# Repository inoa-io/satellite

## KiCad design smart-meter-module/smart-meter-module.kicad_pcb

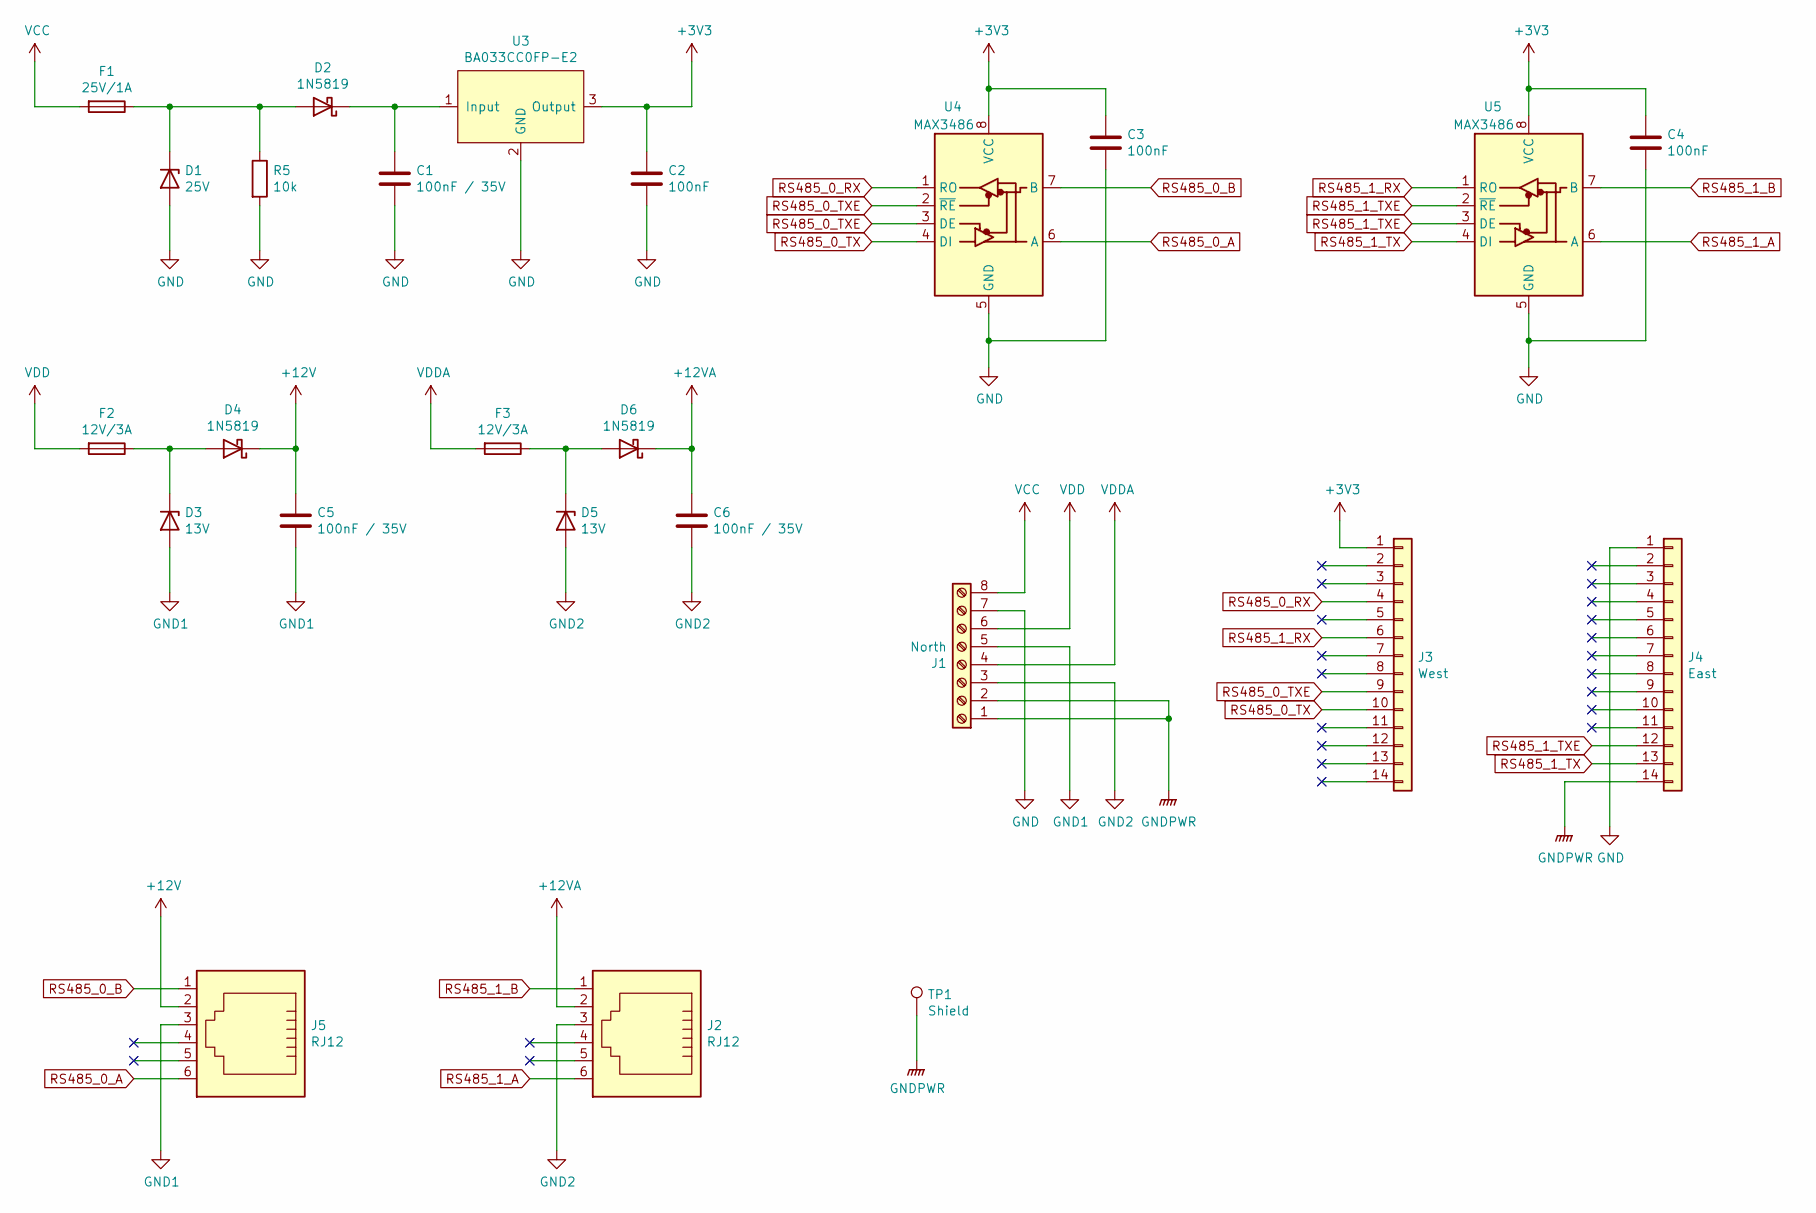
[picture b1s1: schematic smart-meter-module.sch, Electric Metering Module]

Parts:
C1, C5, C6: 100nF / 35V; C_1206_3216Metric_Pad1.33x1.80mm_HandSolder
C2, C3, C4: 100nF; C_1206_3216Metric_Pad1.33x1.80mm_HandSolder
D1: 25V; D_SOD-523
D2, D4, D6: 1N5819; D_SOD-323_HandSoldering
D3, D5: 13V; D_SOD-523
F1: 25V/1A; Fuse_1206_3216Metric_Pad1.42x1.75mm_HandSolder
F2, F3: 12V/3A; Fuse_1206_3216Metric_Pad1.42x1.75mm_HandSolder
J1: North; PHOENIX_1727078
J2, J5: RJ12; Molex-95501-6669-MFG
J3: West; PinHeader_1x14_P2.54mm_Vertical
J4: East; PinHeader_1x14_P2.54mm_Vertical
R5: 10k; R_1206_3216Metric_Pad1.30x1.75mm_HandSolder
TP1: Shield; TestPoint_Pad_D4.0mm
U3: BA033CC0FP-E2; TO-252-3_TabPin2
U4, U5: MAX3486; SOIC-8_3.9x4.9mm_P1.27mm

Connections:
+3V3: C2.1, C3.1, C4.1, J3.1, U3.3 (Output), U4.8 (VCC), U5.8 (VCC)
+12V: C5.1, D4.1 (K), J5.2
+12VA: C6.1, D6.1 (K), J2.2
GND: C1.2, C2.2, C3.2, C4.2, D1.2 (A), J1.7, J4.1, R5.2, U3.2 (GND), U4.5 (GND), U5.5 (GND)
GND1: C5.2, D3.2 (A), J1.5, J5.3
GND2: C6.2, D5.2 (A), J1.3, J2.3
GNDPWR: J1.1, J1.2, J4.14, TP1.1
unnamed: C1.1, D2.1 (K), U3.1 (Input)
unnamed: D1.1 (K), D2.2 (A), F1.1, R5.1
unnamed: D3.1 (K), D4.2 (A), F2.1
unnamed: D5.1 (K), D6.2 (A), F3.1
RS485_0_A: J5.6, U4.6 (A)
RS485_0_B: J5.1, U4.7 (B)
RS485_0_RX: J3.4, U4.1 (RO)
RS485_0_TX: J3.10, U4.4 (DI)
RS485_0_TXE: J3.9, U4.2 (~RE), U4.3 (DE)
RS485_1_A: J2.6, U5.6 (A)
RS485_1_B: J2.1, U5.7 (B)
RS485_1_RX: J3.6, U5.1 (RO)
RS485_1_TX: J4.13, U5.4 (DI)
RS485_1_TXE: J4.12, U5.2 (~RE), U5.3 (DE)
VCC: F1.2, J1.8
VDD: F2.2, J1.6
VDDA: F3.2, J1.4

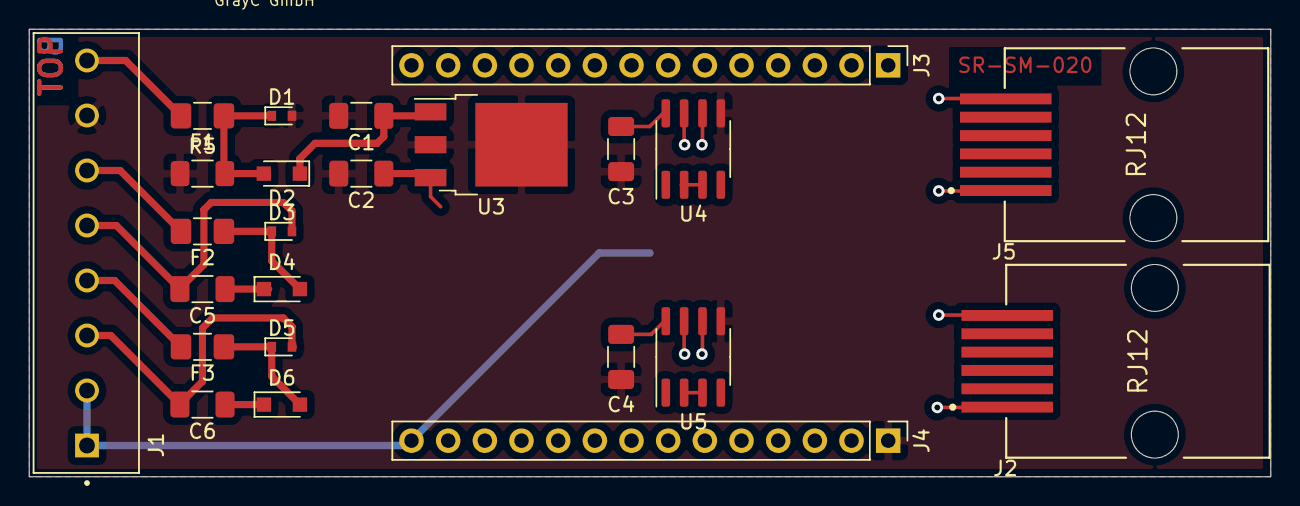
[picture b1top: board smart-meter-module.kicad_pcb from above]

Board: 2 copper layers, 86.0 x 31.0 mm, 25 parts (1 on the bottom side), 24 nets.

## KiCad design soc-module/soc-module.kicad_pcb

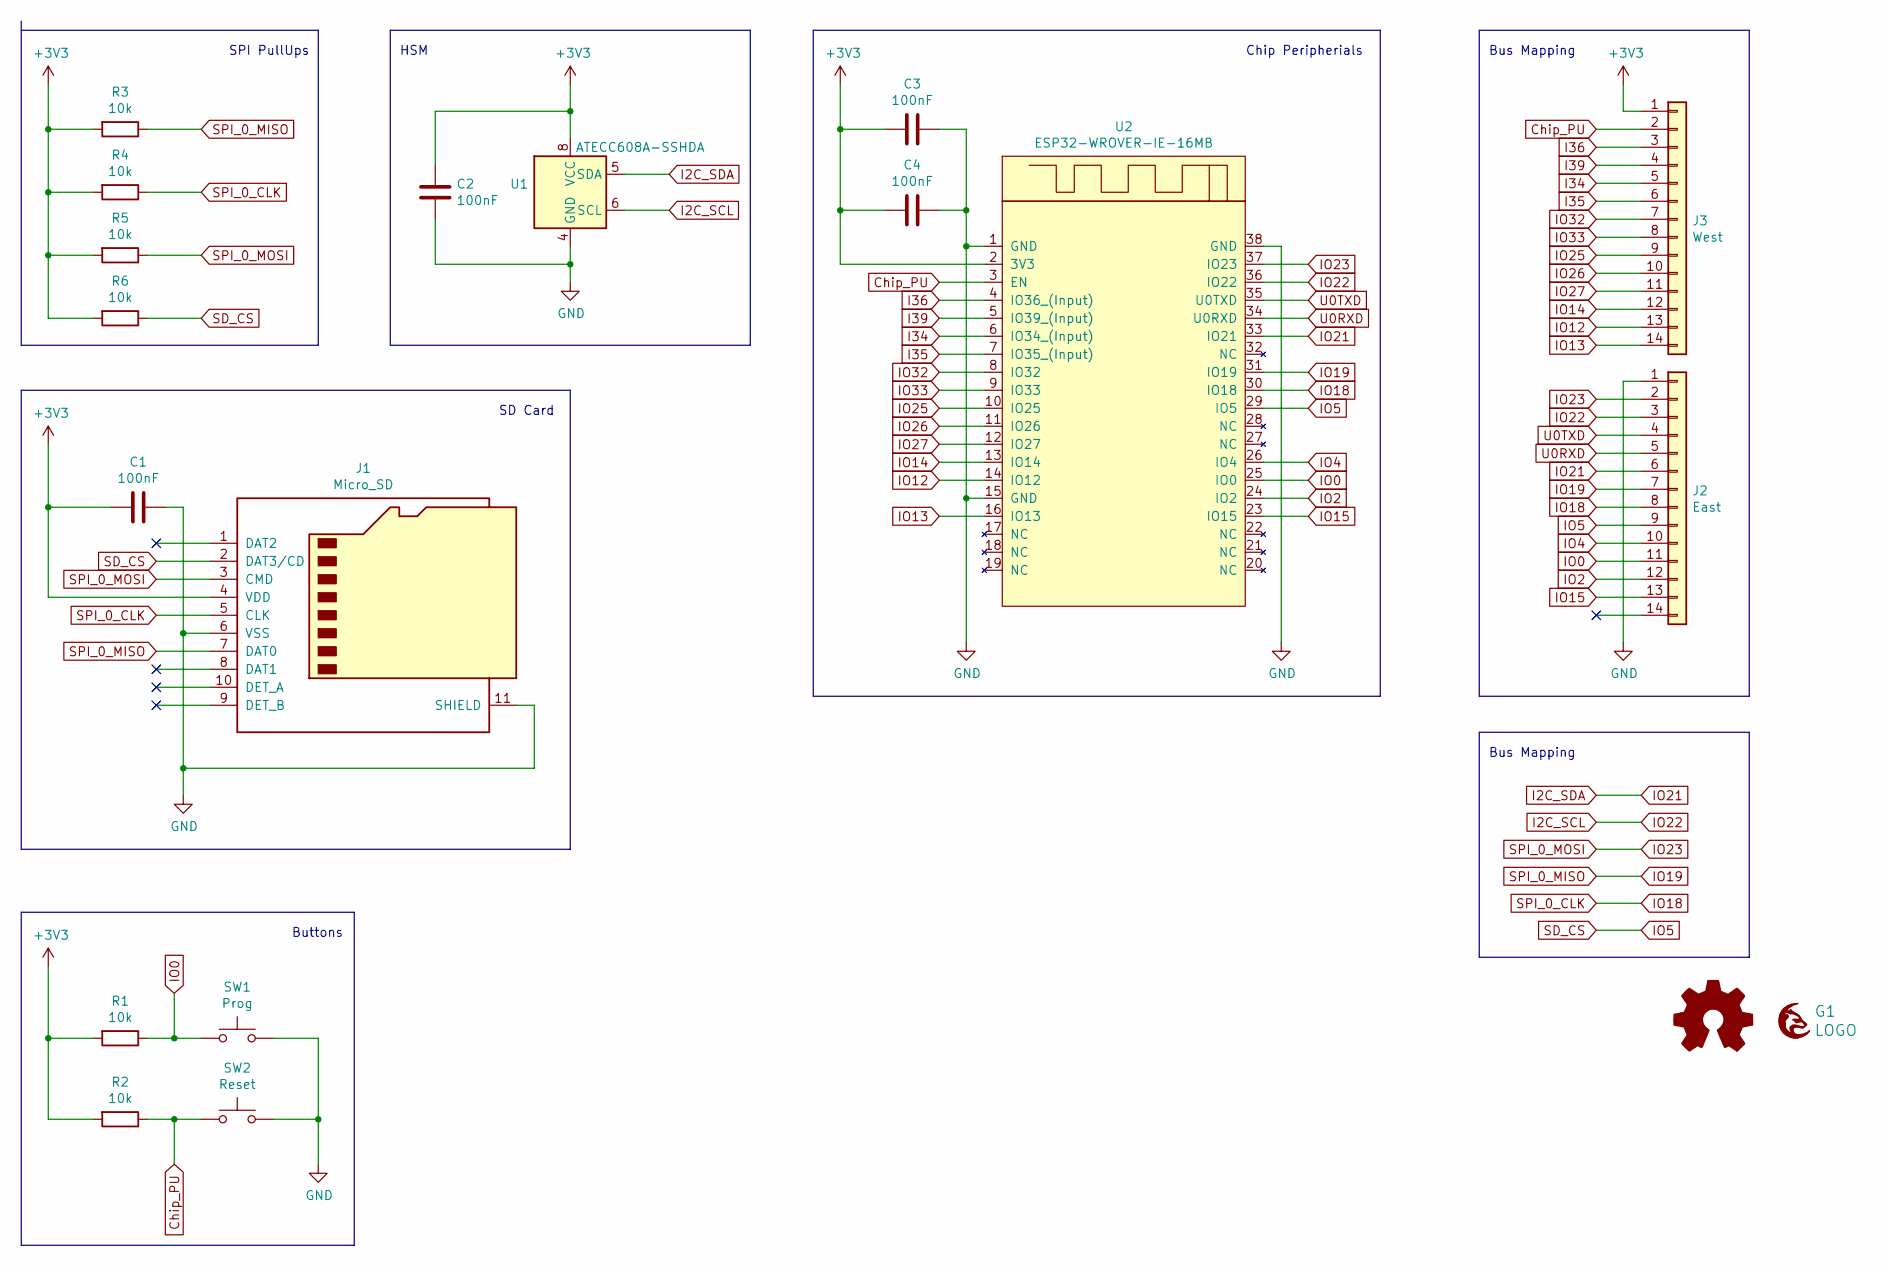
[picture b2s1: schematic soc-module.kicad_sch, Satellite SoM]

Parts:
C1, C2, C3, C4: 100nF; C_1206_3216Metric_Pad1.33x1.80mm_HandSolder
G1: LOGO; grayc-logo-negative
G2: Logo_Open_Hardware_Small; OSHW-Logo2_7.3x6mm_SilkScreen
J1: Micro_SD; GCT_MEM2061-01-188-00-A_REVA
J2: East; PinHeader_1x14_P2.54mm_Vertical
J3: West; PinHeader_1x14_P2.54mm_Vertical
R1, R2, R3, R4, R5, R6: 10k; R_1206_3216Metric_Pad1.30x1.75mm_HandSolder
SW1: Prog; SW4SMD_63X161LS
SW2: Reset; SW4SMD_63X161LS
U1: ATECC608A-SSHDA; SOIC-8_3.9x4.9mm_P1.27mm
U2: ESP32-WROVER-IE-16MB; ESP32-WROVER

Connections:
+3V3: C1.2, C2.1, C3.2, C4.2, J1.4 (VDD), J3.1, R1.2, R2.2, R3.2, R4.2, R5.2, R6.2, U1.8 (VCC), U2.2 (3V3)
Chip_PU: J3.2, R2.1, SW2.1, U2.3 (EN)
GND: C1.1, C2.2, C3.1, C4.1, J1.6 (VSS), J1.11 (SHIELD), J2.1, SW1.2, SW2.2, U1.4 (GND), U2.1 (GND), U2.15 (GND), U2.38 (GND)
I2C_SCL: J2.3, U1.6 (SCL), U2.36 (IO22)
I2C_SDA: J2.6, U1.5 (SDA), U2.33 (IO21)
I34: J3.5, U2.6 (IO34_(Input))
I35: J3.6, U2.7 (IO35_(Input))
I36: J3.3, U2.4 (IO36_(Input))
I39: J3.4, U2.5 (IO39_(Input))
IO0: J2.11, R1.1, SW1.1, U2.25 (IO0)
IO2: J2.12, U2.24 (IO2)
IO4: J2.10, U2.26 (IO4)
IO5: J1.2 (DAT3/CD), J2.9, R6.1, U2.29 (IO5)
IO12: J3.13, U2.14 (IO12)
IO13: J3.14, U2.16 (IO13)
IO14: J3.12, U2.13 (IO14)
IO15: J2.13, U2.23 (IO15)
IO18: J1.5 (CLK), J2.8, R4.1, U2.30 (IO18)
IO19: J1.7 (DAT0), J2.7, R3.1, U2.31 (IO19)
IO23: J1.3 (CMD), J2.2, R5.1, U2.37 (IO23)
IO25: J3.9, U2.10 (IO25)
IO26: J3.10, U2.11 (IO26)
IO27: J3.11, U2.12 (IO27)
IO32: J3.7, U2.8 (IO32)
IO33: J3.8, U2.9 (IO33)
U0RXD: J2.5, U2.34 (U0RXD)
U0TXD: J2.4, U2.35 (U0TXD)

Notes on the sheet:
Buttons
HSM
SPI PullUps
Chip Peripherials
Bus Mapping
SD Card

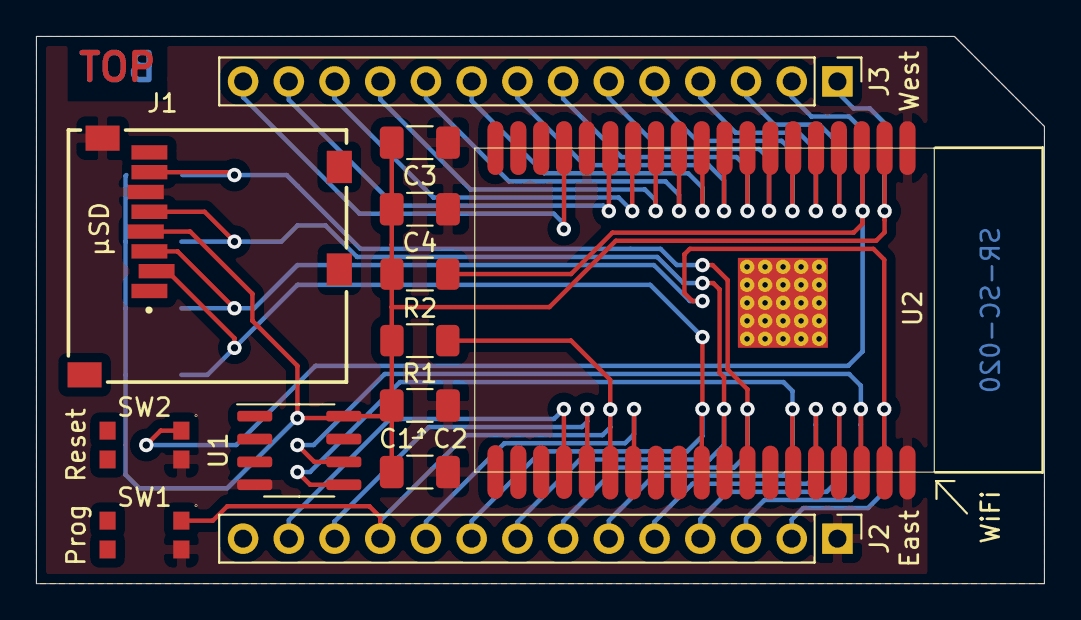
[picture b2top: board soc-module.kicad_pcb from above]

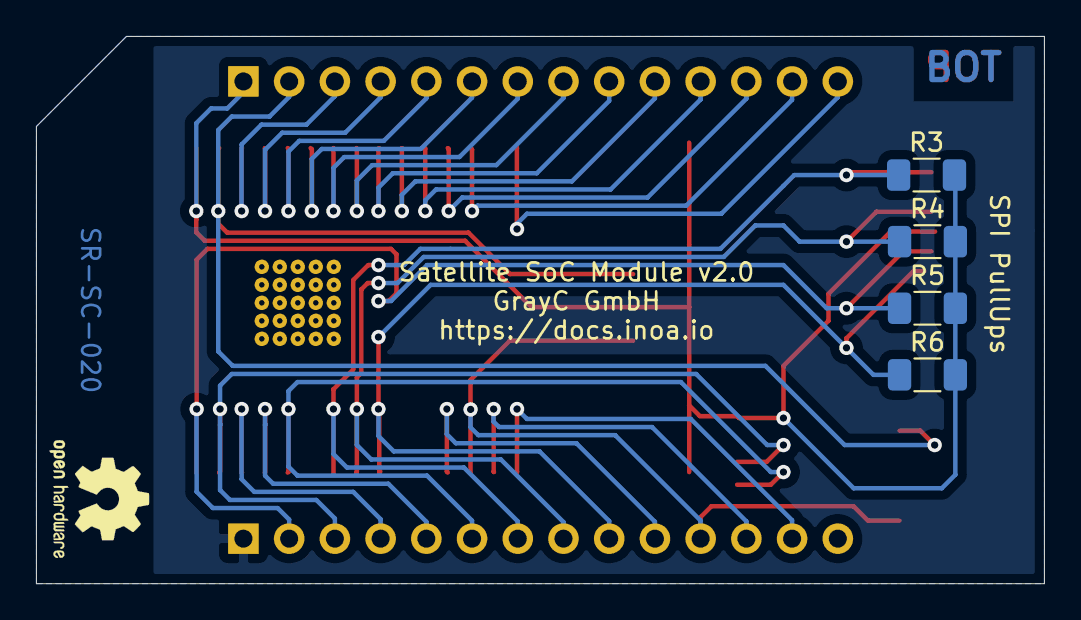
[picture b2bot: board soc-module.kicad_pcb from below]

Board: 2 copper layers, 56.0 x 30.4 mm, 19 parts (6 on the bottom side), 27 nets.
